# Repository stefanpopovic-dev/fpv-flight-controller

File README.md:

# STM32F405 FPV Flight Controller

An open-hardware, 4-layer FPV flight controller board built around the **STM32F405RGT6**, designed in KiCad. Currently at hardware revision **REV3**. Designed to run **Betaflight**.

## Flight video

> 🎥 **Flight video coming soon.**
>
> <!-- Replace this block with the video. Easiest option: edit this README on github.com and drag-and-drop an .mp4 here
>      (GitHub embeds it inline), or link a YouTube video with a thumbnail:
>       -->

## 3D renders

## Real build photos

These photos are of the **previous manufactured and tested revision** of this board (see the Disclaimer section below for what changed in REV3).

| Top | Bottom |
|---|---|
|  |  |

| Installed in the frame | Finished quad (top) | Finished quad (front) |
|---|---|---|
|  |  |  |

## Features

- **MCU:** STM32F405RGT6 (Arm Cortex-M4F, 168 MHz) — the same MCU family used by most Betaflight/iNav AIO flight controllers
- **IMU:** InvenSense ICM-42688-P 6-axis gyro/accelerometer (SPI)
- **Barometer:** Infineon DPS310 for altitude hold / GPS rescue
- **OSD:** MAX7456 analog on-screen display (camera in / VTX out video overlay)
- **Blackbox flash:** Winbond W25Q128JVP, 128 Mbit SPI NOR flash
- **Power:**
  - LMR51635 synchronous buck converter — VBAT down to a regulated 5V rail for the FC and video/VTX peripherals
  - AP2112K-3.3 LDO for the 3.3V digital rail, with a separately filtered +3.3VA analog rail for the IMU
- **USB:** USB-C receptacle with USBLC6-2SC6 ESD protection for DFU flashing / configurator access
- **I/O:** 5 UARTs broken out (UART1, UART2, UART3, UART5), 4 motor signal outputs (M1–M4), current sensor input, buzzer, status LED, boot/reset button, SWD programming header, and general purpose AUX/GPIO pads
- **Board:** 4-layer stack-up (signal / GND plane / power plane / signal)

## Schematic

Full-resolution PDF: [`SCHEMATIC_PDF/REV3.pdf`](SCHEMATIC_PDF/REV3.pdf)

## PCB layout (copper layers)

| Top copper | Bottom copper |
|---|---|
|  |  |

## Connector map

Reference the top-side silkscreen (visible in the top 3D render above) for exact pad locations. Grouped by function:

| Header | Signals |
|---|---|
| SWD / debug | `SWDIO`, `SWCLK`, `GND`, `3.3V`, `U5_TX` |
| Status LED | `LED`, `5V`, `GND` |
| UART1 (GPS / receiver) | `U1_RX`, `U1_TX`, `5V`, `GND` |
| UART3 (VTX / camera) | `U3_TX`, `U3_RX`, `5V`, `GND`, `VOUT` |
| Power in | `VIN`, `5V`, `GND` |
| UART2 | `U2_RX`, `U2_TX`, `5V`, `GND` |
| Motor / ESC connector | `M1`, `M2`, `M3`, `M4`, `VBAT`, `GND`, `CUR_S` (current sense), `U5_RX` (ESC telemetry) |
| AUX | `AUX_P1`, `AUX_P2`, `GPIO1`, `5V`, `GND` |
| Buzzer | `BUZZ`, `5V` |

## Repository structure

```
.
├── hardware/            KiCad 10 project (schematic, PCB, project settings)
│   ├── REV3.kicad_pro
│   ├── REV3.kicad_sch
│   ├── REV3.kicad_pcb
│   ├── REV3.kicad_prl
│   └── fp-lib-table
├── SCHEMATIC_PDF/
│   └── REV3.pdf         Exported schematic PDF
└── docs/
    └── images/          3D renders, copper layer renders, schematic export
        └── photos/      Real photos of the built board and quad
```

## Opening the project

The design was created in **KiCad 10.0**. Open `hardware/REV3.kicad_pro` in KiCad to view/edit the schematic and PCB.

## Firmware compatibility

Built for **Betaflight**. Every IC on this board is natively supported by Betaflight:

- STM32F405RGT6 — supported target MCU family
- ICM-42688-P — supported gyro/accelerometer
- MAX7456 — supported OSD chip
- W25Q128JVP — supported blackbox flash

Since this is a custom PCB (not a stock/off-the-shelf target), it needs a **custom unified target** in Betaflight Configurator with resource mapping matching this schematic's pin assignments: gyro on SPI1 (`PA5`/`PA6`/`PA7`, CS `PA4`), OSD on SPI2 (`PB12`/`PB14`/`PB15`, CS `PB11`), blackbox flash on SPI3 (`PB3`/`PB4`/`PB5`, CS `PA15`), motors `M1`–`M4` on `PB0`/`PB1`/`PC6`/`PC7`, and UART1/2/3/5 as broken out on the connectors above — see the schematic for the full pin list. No target file is included in this repo yet.

## Status / notes

- This repository currently contains the hardware design only (schematic + PCB). No firmware/target file is included yet.
- DRC exclusions present in the board file are inherited from the source project and should be reviewed before fabrication.

## ⚠️ Disclaimer

**This exact revision (REV3) has not been manufactured or tested yet.** It is a corrected revision of a previously manufactured and tested board, so it is very similar to a known-working unit but has not itself been built/verified. The fixes made since the last manufactured/tested version:

- The barometer (DPS310) was not connected to 3.3V — fixed.
- The boot/reset button was tied high and did not function — fixed.

The [real build photos](#real-build-photos) above show that previous tested revision; photos of a REV3 unit will be added once it is built.

## License

Licensed under the [CERN Open Hardware Licence Version 2 - Strongly Reciprocal (CERN-OHL-S v2)](LICENSE). Anyone who manufactures or modifies this design must make their modified source available under the same licence.

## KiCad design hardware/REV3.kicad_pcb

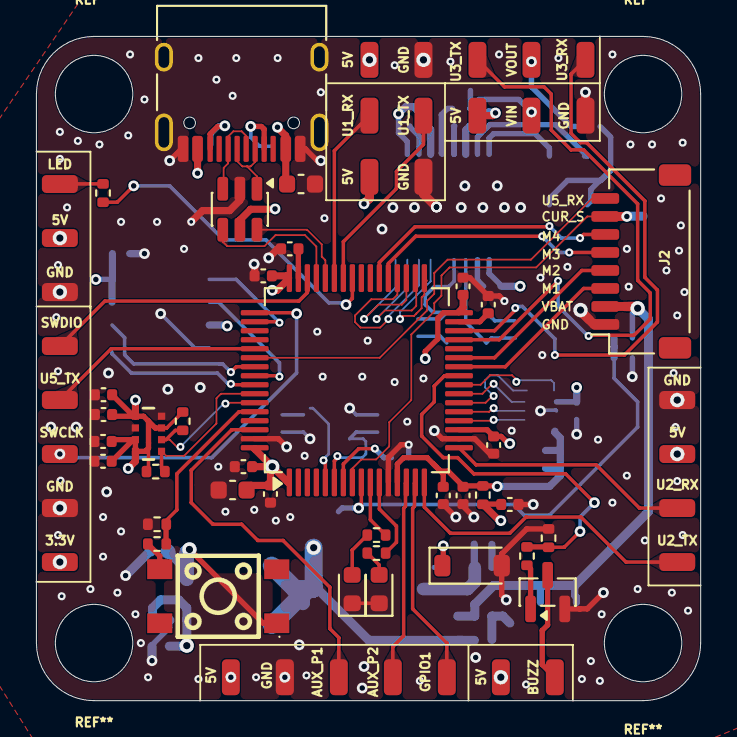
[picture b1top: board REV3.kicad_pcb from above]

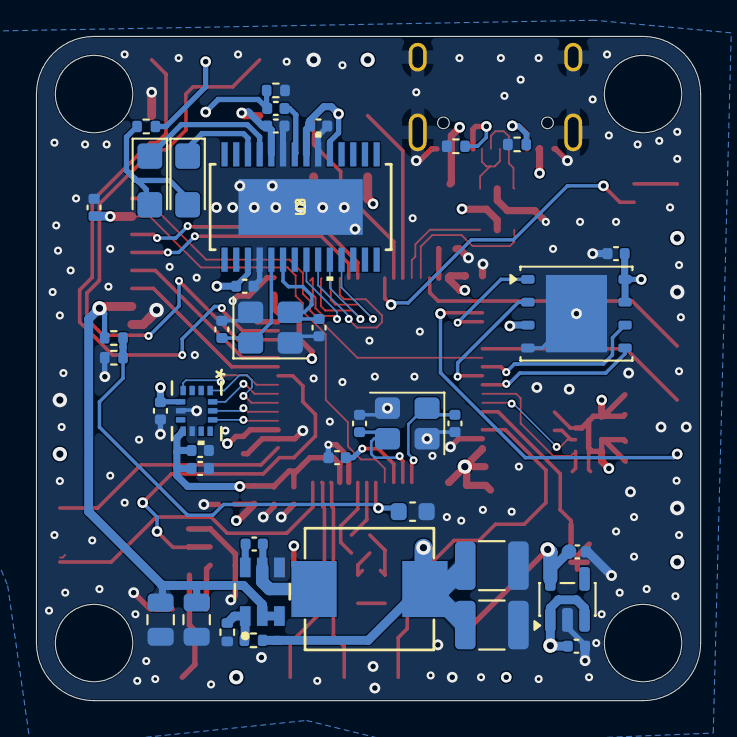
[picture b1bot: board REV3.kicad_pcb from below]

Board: 4 copper layers, 36.9 x 36.9 mm, 107 parts (40 on the bottom side), 72 nets.

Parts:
3.3V, 5V#7: Conn_01x01_Pin; SolderWirePad_1x01_SMD_1x2mm
5V: VTX; SolderWirePad_1x01_SMD_1x2mm
5V#2: GPS; SolderWirePad_1x01_SMD_1x2mm
5V#3: CAM; SolderWirePad_1x01_SMD_1x2mm
5V#4: EXTRA; SolderWirePad_1x01_SMD_1x2mm
5V#5: Buzzer5v; SolderWirePad_1x01_SMD_1x2mm
5V#6: ELRS; SolderWirePad_1x01_SMD_1x2mm
AUX_P1, AUX_P2: EXTRA; SolderWirePad_1x01_SMD_1x2mm
BUZZ: Buzzer2; SolderWirePad_1x01_SMD_1x2mm
C2, C3, C4, C5, C6, C11: 100n; C_0402_1005Metric
C7: 10u; C_0603_1608Metric
C8: 10n; C_0402_1005Metric
C9, C10: 1u; C_0402_1005Metric
C12, C13: 18pF; C_0402_1005Metric
C14, C23, C24, C25, C31: 100nF; C_0402_1005Metric
C15: 10uF; C_0603_1608Metric
C16, C36: 10nF; C_0402_1005Metric
C17, C32, C33, C39, C41: 2.2uF; C_0402_1005Metric
C18, C38, C40: 0.1uF; C_0402_1005Metric
C19, C20: 47uF; CP_EIA-3216-18_Kemet-A
C21, C22: 15pF; C_0402_1005Metric
CBOOT1: 0.1uF; C_0402_1005Metric
COUT1, COUT3: 33uF; C_1210_3225Metric
COUT2, COUT4: 1uF; C_0402_1005Metric
Cin2: 2.2uF; C_0805_2012Metric
Cin3: 100nF; C_0603_1608Metric
Cin5: 0.1uF; C_0805_2012Metric
D1: D; D_SOD-123
D2, D3: LED; LED_0603_1608Metric
FB1: 120R; R_0402_1005Metric
GND: EXTRA; SolderWirePad_1x01_SMD_1x2mm
GND#2: GPS; SolderWirePad_1x01_SMD_1x2mm
GND#3, GND#7: Conn_01x01_Pin; SolderWirePad_1x01_SMD_1x2mm
GND#4: CAM; SolderWirePad_1x01_SMD_1x2mm
GND#5: VTX; SolderWirePad_1x01_SMD_1x2mm
GND#6: ELRS; SolderWirePad_1x01_SMD_1x2mm
GPIO1: EXTRA; SolderWirePad_1x01_SMD_1x2mm
GYRO1: ICM-42688-P; LGA14_2P5X3X0P91_TDK
J1: USB_C_Receptacle_USB2.0_14P; USB_C_Receptacle_HRO_TYPE-C-31-M-12
J2: Conn_01x08; JST_SH_SM08B-SRSS-TB_1x08-1MP_P1.00mm_Horizontal
L1: MDA7050-100M; IND-SMD_L7.3-W6.6_MHCI06030
LED: Conn_01x01_Pin; SolderWirePad_1x01_SMD_1x2mm
Q1: 2N7002; SOT-23
R1, R14: 330; R_0402_1005Metric
R2: 53.6kΩ; R_0402_1005Metric
R3: 10.2kΩ; R_0402_1005Metric
R4, R5: 5k1; R_0402_1005Metric
R8, R9: 330R; R_0402_1005Metric
R10: 100R; R_0402_1005Metric
R11: 10kR; R_0402_1005Metric
R12, R13: 75; R_0402_1005Metric
R15, R17: 10k; R_0402_1005Metric
R16: 1k; R_0402_1005Metric
R20, R21: 4.7k; R_0402_1005Metric
SW1: SW_Push; SW-SMD_4P-L4.5-W4.5-P3.00-LS6.8
SWCLK: Conn_01x01_Pin; SolderWirePad_1x01_SMD_1x2mm
SWDIO: Conn_01x01_Pin; SolderWirePad_1x01_SMD_1x2mm
U1: STM32F405RGT6; LQFP-64_10x10mm_P0.5mm
U1_RX, U1_TX: ELRS; SolderWirePad_1x01_SMD_1x2mm
U2: USBLC6-2SC6; SOT-23-6
U2_RX, U2_TX: GPS; SolderWirePad_1x01_SMD_1x2mm
U3: DPS310; PG-VLGA-8-1_INF
U3_RX, U3_TX: VTX; SolderWirePad_1x01_SMD_1x2mm
U4: AP2112K-3.3; SOT-23-5
U5: W25Q128JVP; WSON-8-1EP_6x5mm_P1.27mm_EP3.4x4.3mm
U5_TX: Conn_01x01_Pin; SolderWirePad_1x01_SMD_1x2mm
U6: LMR51635XDDCR; DDC0006A-MFG
U8: AT7456; 21-0108G_U28E-5_MXM
VIN: CAM; SolderWirePad_1x01_SMD_1x2mm
VOUT: VTX; SolderWirePad_1x01_SMD_1x2mm
Y1: 8MHz; Crystal_SMD_3225-4Pin_3.2x2.5mm
Y2: 27MHZ; Crystal_SMD_3225-4Pin_3.2x2.5mm

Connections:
+3.3V: 3.3V.1 (Pin_1_1), C2.1, C3.1, C4.1, C5.1, C6.1, C7.1, C10.1, C14.2, C16.1, C38.1, C39.1, C40.1, C41.1, COUT2.2, FB1.2, GYRO1.5 (VDDIO), R20.2, R21.2, SW1.1, SW1.3, U1.1 (VBAT), U1.19 (VDD), U1.32 (VDD), U1.48 (VDD), U1.64 (VDD), U3.2 (CSB), U3.5 (SDO), U3.6 (VDDIO), U3.8 (VDD), U4.5 (VOUT), U5.3 (~WP/IO_{2}), U5.7 (~HOLD/~RESET/IO_{3}), U5.8 (VCC)
+3.3VA: C8.1, C9.1, C17.2, C18.2, FB1.1, GYRO1.8 (VDD), U1.13 (VDDA)
+5V: 5V.1 (Pin_1_1), 5V#2.1 (Pin_1_1), 5V#3.1 (Pin_1_1), 5V#4.1 (Pin_1_1), 5V#5.1 (Pin_1_1), 5V#6.1 (Pin_1_1), 5V#7.1 (Pin_1_1), C15.1, C23.1, C24.2, C25.1, COUT1.2, COUT3.2, COUT4.2, D1.1 (K), J1.A4 (VBUS), J1.A9 (VBUS), J1.B4 (VBUS), J1.B9 (VBUS), L1.2, R2.2, U2.5 (VBUS), U4.1 (VIN), U4.3 (EN), U8.3 (DVDD), U8.19 (~RESET), U8.21 (AVDD), U8.24 (PVDD)
/BOOT0: R1.2, R17.2, U1.60 (BOOT0)
/NRST: C11.1, U1.7 (NRST)
/SW_BOOT0: R1.1, SW1.2, SW1.4
/VIDEO OUT: R12.2, VOUT.1 (Pin_1_1)
AUX_GPIO1: GPIO1.1 (Pin_1_1), U1.15 (PA1)
AUX_PWM1: AUX_P1.1 (Pin_1_1), U1.62 (PB9)
AUX_PWM2: AUX_P2.1 (Pin_1_1), U1.14 (PA0)
BUZZER: R10.2, R11.2, U1.25 (PC5)
CLKIN: C21.1, U8.5 (CLKIN), Y2.1
CURRENT_SENSE: C36.2, J2.7, U1.8 (PC0)
FLASH_CS: U1.50 (PA15), U5.1 (~CS)
GND: C2.2, C3.2, C4.2, C5.2, C6.2, C7.2, C8.2, C9.2, C10.2, C11.2, C12.2, C13.2, C14.1, C15.2, C16.2, C17.1, C18.1, C21.2, C22.2, C23.2, C24.1, C25.2, C32.2, C33.2, C36.1, C38.2, C39.2, C40.2, C41.2, COUT1.1, COUT2.1, COUT3.1, COUT4.1, Cin2.1, Cin3.1, Cin5.1, D1.2 (A), D2.1 (K), D3.1 (K), GND.1 (Pin_1_1), GND#2.1 (Pin_1_1), GND#3.1 (Pin_1_1), GND#4.1 (Pin_1_1), GND#5.1 (Pin_1_1), GND#6.1 (Pin_1_1), GND#7.1 (Pin_1_1), GYRO1.6 (GND), GYRO1.9 (INT2/FSYNC/CLKIN), J1.A1 (GND), J1.A12 (GND), J1.B1 (GND), J1.B12 (GND), J1.SH (SHIELD), J2.1, Q1.2 (S), R3.1, R4.1, R5.1, R11.1, R13.1, R16.2, R17.1, U1.12 (VSSA), U1.18 (VSS), U1.63 (VSS), U2.2 (GND), U3.1 (GND), U3.7 (GND), U4.2 (GND), U5.4 (GND), U5.9 (EP), U6.4 (GND), U8.4 (DGND), U8.20 (AGND), U8.23 (PGND), U8.EPAD, Y1.2 (G), Y1.4 (G), Y2.2 (G), Y2.4 (G)
GYRO_INT: GYRO1.4 (INT1/INT), U1.24 (PC4)
I2C1_SCL: R20.1, U1.58 (PB6), U3.4 (SCK)
I2C1_SDA: R21.1, U1.59 (PB7), U3.3 (SDI)
IMU_CS: GYRO1.12 (AP_CS), U1.20 (PA4)
LED_STATUS1: R8.1, U1.10 (PC2)
LED_STATUS2: R9.1, U1.11 (PC3)
LED_STRIP: R14.2, U1.41 (PA8)
M1: J2.3, U1.26 (PB0)
M2: J2.4, U1.27 (PB1)
M3: J2.5, U1.37 (PC6)
M4: J2.6, U1.38 (PC7)
unnamed: C19.2, C20.2, R12.1
unnamed: D2.2 (A), R8.2
unnamed: D3.2 (A), R9.2
unnamed: J1.A5 (CC1), R4.2
unnamed: J1.B5 (CC2), R5.2
unnamed: J1.A6 (D+), J1.B6 (D+), U2.3 (I/O2)
unnamed: J1.A7 (D-), J1.B7 (D-), U2.1 (I/O1)
unnamed: LED.1 (Pin_1_1), R14.1
unnamed: BUZZ.1 (Pin_1_1), Q1.3 (D)
unnamed: C31.1, R13.2, VIN.1 (Pin_1_1)
unnamed: Q1.1 (G), R10.1
unnamed: C13.1, U1.5 (PH0), Y1.1
unnamed: C12.1, U1.6 (PH1), Y1.3
unnamed: C32.1, U1.31 (VCAP_1)
unnamed: C33.1, U1.47 (VCAP_2)
unnamed: CBOOT1.1, U6.6 (CB)
unnamed: R2.1, R3.2, U6.1 (FB)
unnamed: CBOOT1.2, L1.1, U6.5 (SW)
OSD_CS: U1.33 (PB12), U8.8 (~CS)
SAG: C20.1, U8.25 (SAG)
SPI1_MISO: GYRO1.1 (AP_SDO/AP_AD0), U1.22 (PA6)
SPI1_MOSI: GYRO1.14 (AP_SDA/AP_SDIO/AP_SDI), U1.23 (PA7)
SPI1_SCK: GYRO1.13 (AP_SCL/AP_SCLK), U1.21 (PA5)
SPI2_MISO: U1.35 (PB14), U8.11 (SDOUT)
SPI2_MOSI: U1.36 (PB15), U8.9 (SDIN)
SPI2_SCK: U1.34 (PB13), U8.10 (SCLK)
SPI3_MISO: U1.56 (PB4), U5.2 (DO/IO_{1})
SPI3_MOSI: U1.57 (PB5), U5.5 (DI/IO_{0})
SPI3_SCK: U1.55 (PB3), U5.6 (CLK)
SWCLK: SWCLK.1 (Pin_1_1), U1.49 (PA14)
SWDIO: SWDIO.1 (Pin_1_1), U1.46 (PA13)
UART5_RX: J2.8, U1.54 (PD2)
UART5_TX: U1.53 (PC12), U5_TX.1 (Pin_1_1)
USART1_RX: U1.43 (PA10), U1_RX.1 (Pin_1_1)
USART1_TX: U1.42 (PA9), U1_TX.1 (Pin_1_1)
USART2_RX: U1.17 (PA3), U2_RX.1 (Pin_1_1)
USART2_TX: U1.16 (PA2), U2_TX.1 (Pin_1_1)
USART3_RX: U1.30 (PB11), U3_RX.1 (Pin_1_1)
USART3_TX: U1.29 (PB10), U3_TX.1 (Pin_1_1)
USB_DM: U1.44 (PA11), U2.6 (I/O1)
USB_DP: U1.45 (PA12), U2.4 (I/O2)
VBAT: Cin2.2, Cin5.2, J2.2, R15.1, U6.2 (EN), U6.3 (VIN)
VBAT_SENSE: Cin3.2, R15.2, R16.1, U1.9 (PC1)
VIN: C31.2, U8.22 (VIN)
VOUT: C19.1, U8.26 (VOUT)
XFB: C22.1, U8.6 (XFB), Y2.3
